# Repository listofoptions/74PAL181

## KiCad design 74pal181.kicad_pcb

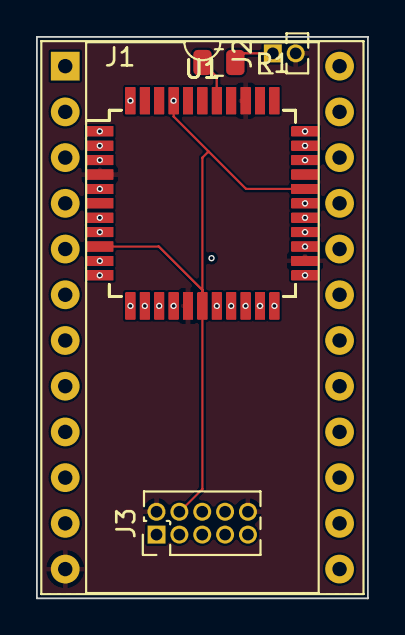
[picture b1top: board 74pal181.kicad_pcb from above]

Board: 4 copper layers, 18.4 x 31.2 mm, 6 parts (0 on the bottom side), 30 nets.

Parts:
J1: aries 24-600-20; DIP-24_W15.24mm_Socket
J2: prog voltage; PinHeader_1x02_P1.27mm_Vertical
J3: FTSH-105-04-F-D; PinHeader_2x05_P1.27mm_Vertical
R1: CPF0805B2K2E1; R_0805_2012Metric
U1: ATF1502AS-xAx44; TQFP-44_10x10mm_P0.8mm
U1#2: ATF1504AS-7AX44; TQFP-44_10x10mm_P0.8mm

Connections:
+5V: J1.24, J3.4 (VREF), U1.9 (VCC), U1.17 (VCC), U1.29 (VCC), U1.41 (VCC), U1#2.9 (VCC), U1#2.17 (VCC), U1#2.29 (VCC), U1#2.41 (VCC)
+12V: J2.1, R1.2
/A=B: J1.14, U1.19 (I/O/PD2), U1#2.19 (I/O/PD2)
/C_{N+4}: J1.16, U1.21 (I/O), U1#2.21 (I/O)
/C_{N}: J1.7, U1.11 (I/O), U1#2.11 (I/O)
/M: J1.8, U1.12 (I/O), U1#2.12 (I/O)
/S0: J1.6, U1.10 (I/O), U1#2.10 (I/O)
/S1: J1.5, U1.8 (I/O), U1#2.8 (I/O)
/S2: J1.4, U1.5 (I/O/PD1), U1#2.5 (I/O/PD1)
/S3: J1.3, U1.3 (I/O), U1#2.3 (I/O)
/TCK: J3.1 (TCK), U1.26 (I/O/TCK), U1#2.26 (I/O/TCK)
/TDI: J3.9 (TDI), U1.1 (I/O/TDI), U1#2.1 (I/O/TDI)
/TDO: J3.3 (TDO), U1.32 (I/O/TDO), U1#2.32 (I/O/TDO)
/TMS: J3.5 (TMS), U1.7 (I/O/TMS), U1#2.7 (I/O/TMS)
/~A0: J1.2, U1.2 (I/O), U1#2.2 (I/O)
/~A1: J1.23, U1.33 (I/O), U1#2.33 (I/O)
/~A2: J1.21, U1.28 (I/O), U1#2.28 (I/O)
/~A3: J1.19, U1.25 (I/O), U1#2.25 (I/O)
/~B0: J1.1, U1.44 (I/O), U1#2.44 (I/O)
/~B1: J1.22, U1.31 (I/O), U1#2.31 (I/O)
/~B2: J1.20, U1.27 (I/O), U1#2.27 (I/O)
/~B3: J1.18, U1.23 (I/O), U1#2.23 (I/O)
/~F0: J1.9, U1.13 (I/O), U1#2.13 (I/O)
/~F1: J1.10, U1.14 (I/O), U1#2.14 (I/O)
/~F2: J1.11, U1.15 (I/O), U1#2.15 (I/O)
/~F3: J1.13, U1.18 (I/O), U1#2.18 (I/O)
/~G: J1.17, U1.22 (I/O), U1#2.22 (I/O)
/~P: J1.15, U1.20 (I/O), U1#2.20 (I/O)
GND: J1.12, J2.2, J3.2 (GND), J3.10 (GND), U1.4 (GND), U1.16 (GND), U1.24 (GND), U1.36 (GND), U1#2.4 (GND), U1#2.16 (GND), U1#2.24 (GND), U1#2.36 (GND)
unnamed: R1.1, U1.38 (I/OE1/Vpp), U1#2.38 (I/OE1/Vpp)

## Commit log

2023-04-13 initial commit, probably doesnt work out of the box
2023-04-13 forgot to make A=B pin open collector
